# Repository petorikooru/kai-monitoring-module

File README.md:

# KAI Monitoring Device

This is a repository for Monitoring Device. Built using ESP-IDF v6 Framework.

> [!WARNING]
> This is still in active development!

## Program Tasks

```mermaid
flowchart LR
    A[ESP32-S3]
    A --> B(Display Task)
    A --> C(Sensor Task)
    A --> D(Network Task)
    A --> E(Eepever Task)

    B --> BA[LVGL]
    B --> BB[LovyanGFX]

    C --> CA[SHT45]
    CA --> CAA[Temperature]
    CA --> CAB[Humidity]

    D --> DA[Ethernet]
    D --> DB[WiFi]
    D --> DC[MQTT]

    DC --> DCA[kai/telemetry/*]

    E --> EA[RS485 to TTL UART]
```

## External Dependencies

- LovyanGFX
- LVGL

## Hardware Requirements

- Eepever 1210N (Through RJ45 RS485 Port)
- SHT45 Temperature and Humidity Sensor
- TTL to RS485 Module
- ST7796 + XPT2046 Resistive Touch LCD Display

## Todo List

- [ ] PCB Design and Printing
- [ ] Full 24h testing
- [ ] Code cleanup and proper documentation
- [ ] Code testing

## Credits

- Alexander Kuznetsov for YD ESP32-S3 Schematic and Footprint

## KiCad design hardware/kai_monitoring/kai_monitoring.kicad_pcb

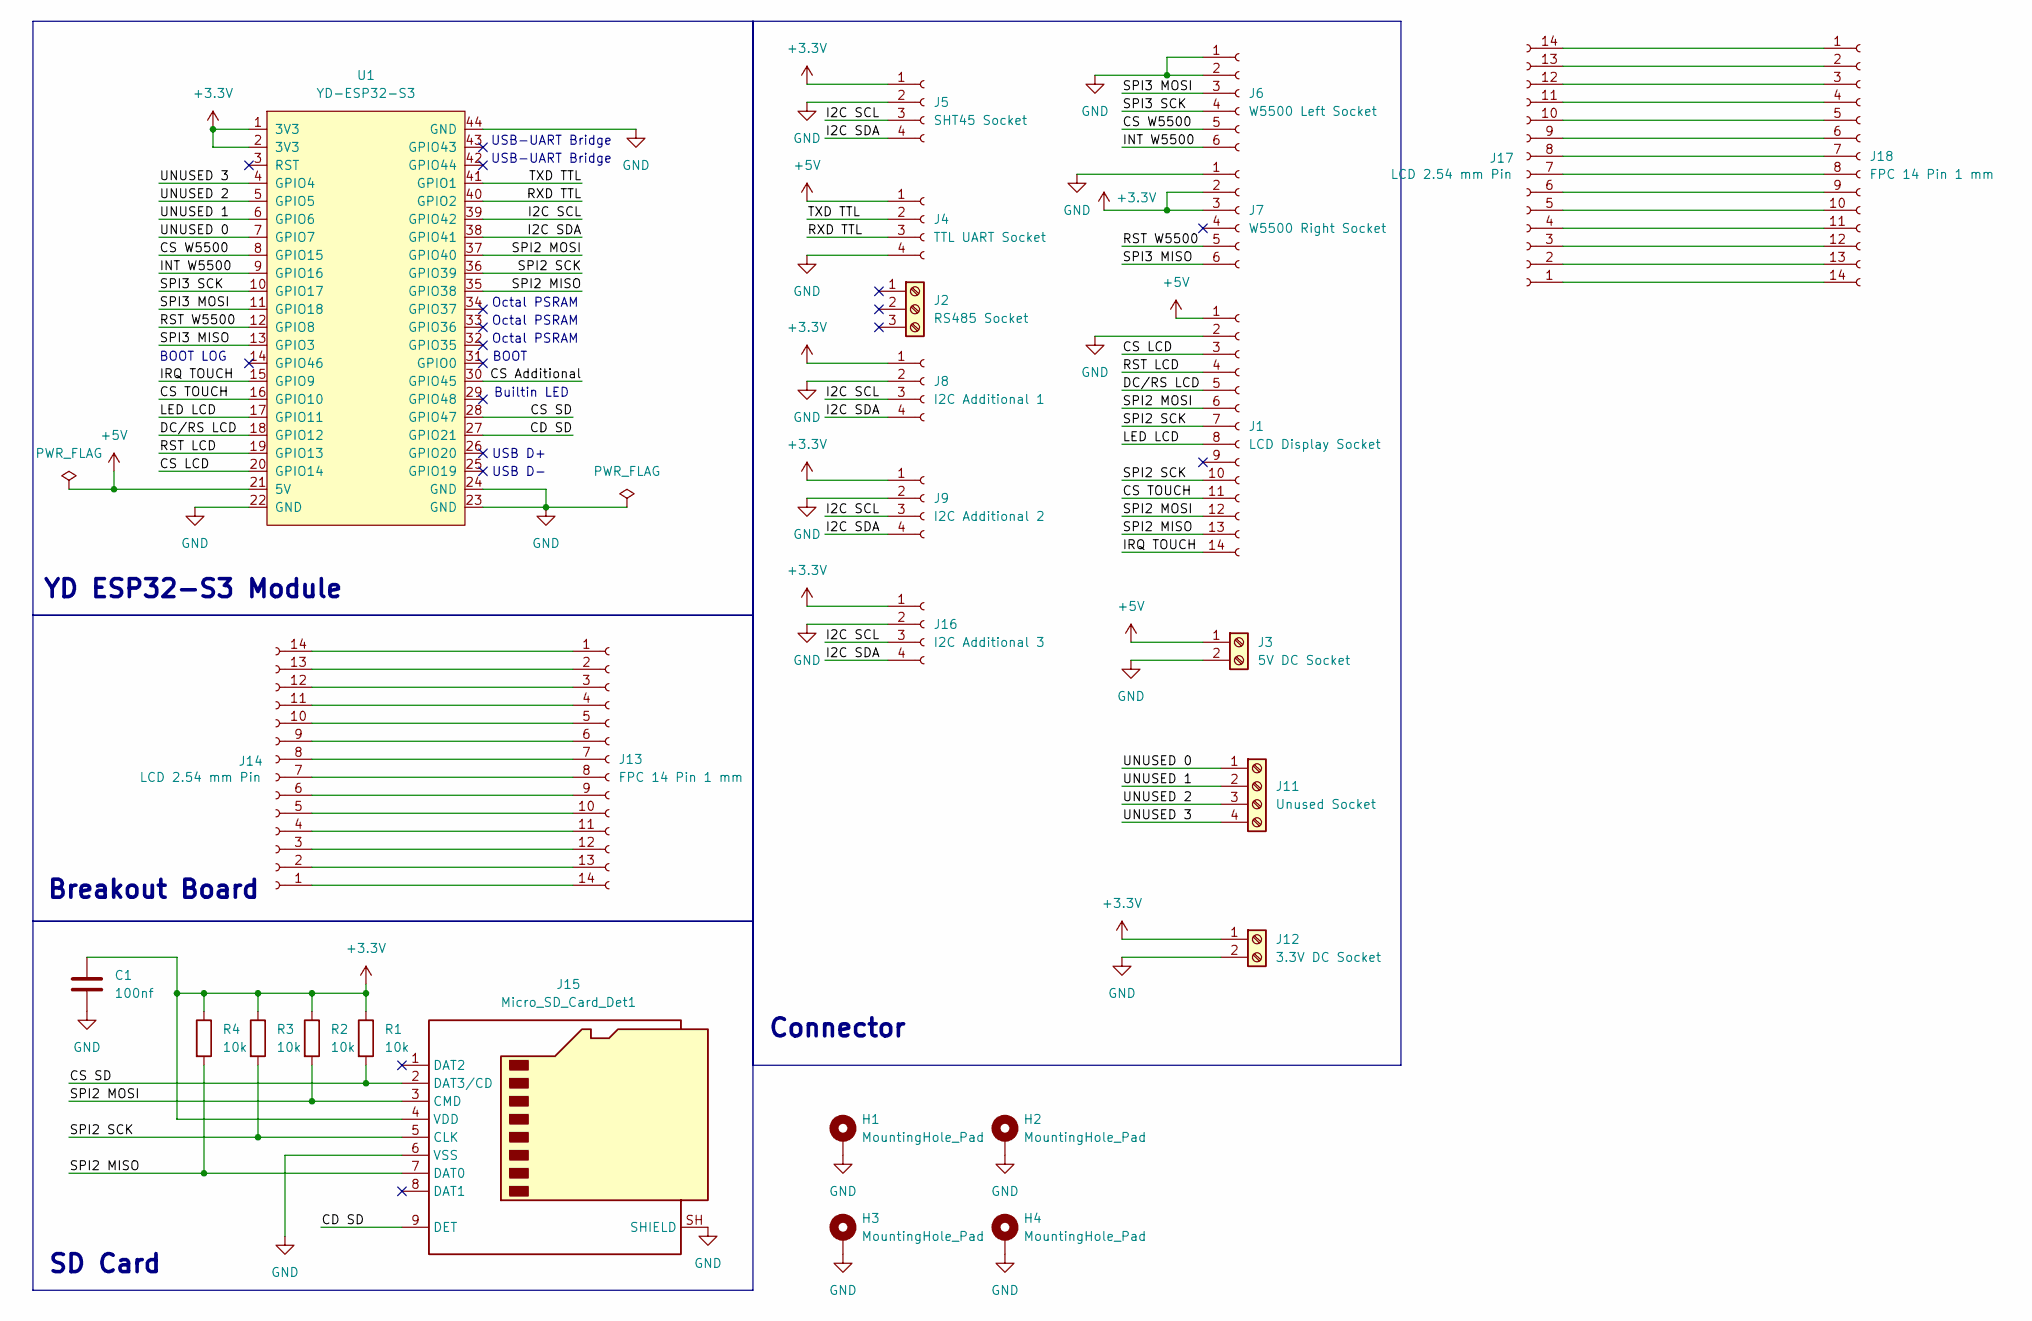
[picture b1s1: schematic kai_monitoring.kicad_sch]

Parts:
C1: 100nf; C_0805_2012Metric
H1, H2, H3, H4: MountingHole_Pad
J1: LCD Display Socket; Molex_200528-0140_1x14-1MP_P1.00mm_Horizontal
J2: RS485 Socket; TerminalBlock_Phoenix_MKDS-1,5-3_1x03_P5.00mm_Horizontal
J3: 5V DC Socket; TerminalBlock_Phoenix_MKDS-3-2-5.08_1x02_P5.08mm_Horizontal
J4: TTL UART Socket; PinSocket_1x04_P2.54mm_Vertical
J5: SHT45 Socket; PinSocket_1x04_P2.54mm_Vertical
J6: W5500 Left Socket; PinSocket_1x06_P2.54mm_Vertical
J7: W5500 Right Socket; PinSocket_1x06_P2.54mm_Vertical
J8: I2C Additional 1; PinSocket_1x04_P2.54mm_Vertical
J9: I2C Additional 2; PinSocket_1x04_P2.54mm_Vertical
J11: Unused Socket; TerminalBlock_Phoenix_MKDS-1,5-4_1x04_P5.00mm_Horizontal
J12: 3.3V DC Socket; TerminalBlock_Phoenix_MKDS-3-2-5.08_1x02_P5.08mm_Horizontal
J13, J18: FPC 14 Pin 1 mm; Molex_200528-0140_1x14-1MP_P1.00mm_Horizontal
J14, J17: LCD 2.54 mm Pin; PinSocket_1x14_P2.54mm_Vertical
J15: Micro_SD_Card_Det1; microSD_HC_Hirose_DM3AT-SF-PEJM5
J16: I2C Additional 3; PinSocket_1x04_P2.54mm_Vertical
R1, R2, R3, R4: 10k; R_0805_2012Metric
U1: YD-ESP32-S3

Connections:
+3.3V: C1.1, J5.1, J7.2, J7.3, J8.1, J9.1, J12.1, J15.4 (VDD), J16.1, R1.1, R2.1, R3.1, R4.1, U1.1 (3V3), U1.2 (3V3)
+5V: J1.1, J3.1, J4.1, U1.21 (5V)
/CD SD: J15.9 (DET), U1.27 (GPIO21)
/CS Additional: U1.30 (GPIO45)
/CS LCD: J1.3, U1.20 (GPIO14)
/CS SD: J15.2 (DAT3/CD), R1.2, U1.28 (GPIO47)
/CS TOUCH: J1.11, U1.16 (GPIO10)
/CS W5500: J6.5, U1.8 (GPIO15)
/DC/RS LCD: J1.5, U1.18 (GPIO12)
/I2C SCL: J5.3, J8.3, J9.3, J16.3, U1.39 (GPIO42)
/I2C SDA: J5.4, J8.4, J9.4, J16.4, U1.38 (GPIO41)
/INT W5500: J6.6, U1.9 (GPIO16)
/IRQ TOUCH: J1.14, U1.15 (GPIO9)
/LED LCD: J1.8, U1.17 (GPIO11)
/RST LCD: J1.4, U1.19 (GPIO13)
/RST W5500: J7.5, U1.12 (GPIO8)
/RXD TTL: J4.3, U1.40 (GPIO2)
/SPI2 MISO: J1.13, J15.7 (DAT0), R4.2, U1.35 (GPIO38)
/SPI2 MOSI: J1.6, J1.12, J15.3 (CMD), R2.2, U1.37 (GPIO40)
/SPI2 SCK: J1.7, J1.10, J15.5 (CLK), R3.2, U1.36 (GPIO39)
/SPI3 MISO: J7.6, U1.13 (GPIO3)
/SPI3 MOSI: J6.3, U1.11 (GPIO18)
/SPI3 SCK: J6.4, U1.10 (GPIO17)
/TXD TTL: J4.2, U1.41 (GPIO1)
/UNUSED 0: J11.1, U1.7 (GPIO7)
/UNUSED 1: J11.2, U1.6 (GPIO6)
/UNUSED 2: J11.3, U1.5 (GPIO5)
/UNUSED 3: J11.4, U1.4 (GPIO4)
GND: C1.2, H1.1, H2.1, H3.1, H4.1, J1.2, J3.2, J4.4, J5.2, J6.1, J6.2, J7.1, J8.2, J9.2, J12.2, J15.6 (VSS), J15.SH (SHIELD), J16.2, U1.22 (GND), U1.23 (GND), U1.24 (GND), U1.44 (GND)
unnamed: J13.1, J14.14
unnamed: J13.2, J14.13
unnamed: J13.3, J14.12
unnamed: J13.4, J14.11
unnamed: J13.5, J14.10
unnamed: J13.6, J14.9
unnamed: J13.7, J14.8
unnamed: J13.8, J14.7
unnamed: J13.9, J14.6
unnamed: J13.10, J14.5
unnamed: J13.11, J14.4
unnamed: J13.12, J14.3
unnamed: J13.13, J14.2
unnamed: J13.14, J14.1
unnamed: J17.1, J18.14
unnamed: J17.2, J18.13
unnamed: J17.3, J18.12
unnamed: J17.4, J18.11
unnamed: J17.5, J18.10
unnamed: J17.6, J18.9
unnamed: J17.7, J18.8
unnamed: J17.8, J18.7
unnamed: J17.9, J18.6
unnamed: J17.10, J18.5
unnamed: J17.11, J18.4
unnamed: J17.12, J18.3
unnamed: J17.13, J18.2
unnamed: J17.14, J18.1

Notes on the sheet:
Octal PSRAM
USB D-
BOOT LOG
USB D+
BOOT
SD Card
USB-UART Bridge
Breakout Board
YD ESP32-S3 Module
Builtin LED
Connector

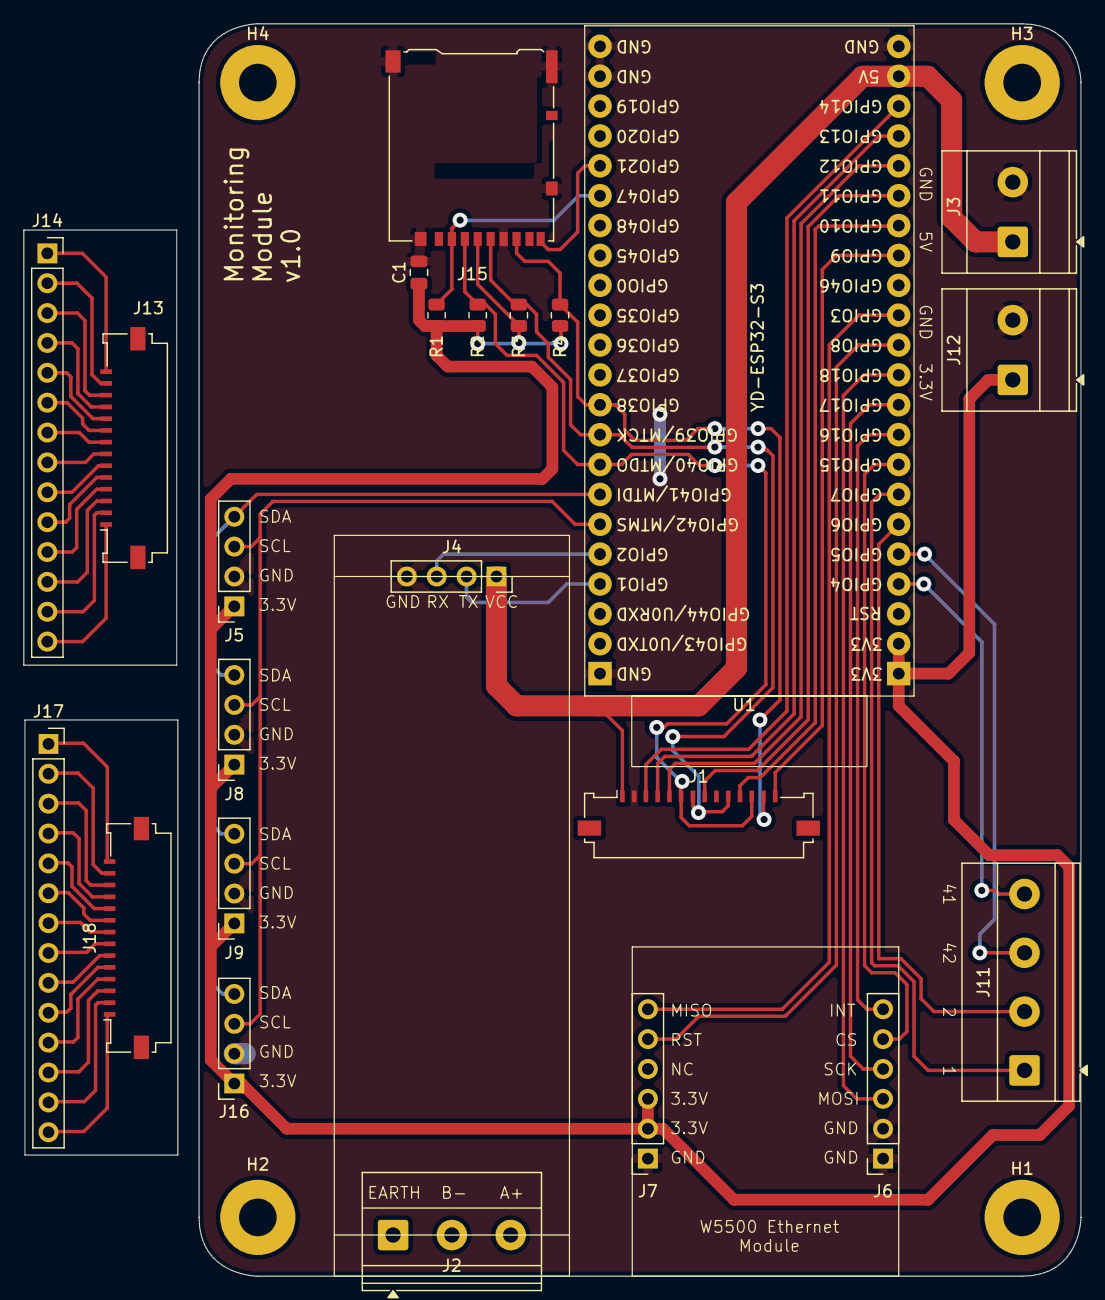
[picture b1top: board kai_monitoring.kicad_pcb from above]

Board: 2 copper layers, 75.0 x 106.5 mm, 27 parts (0 on the bottom side), 56 nets.
